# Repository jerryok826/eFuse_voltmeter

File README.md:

# eFuse Voltmeter

# eFuse Voltmeter in fault

## Project Description
eFuse_Voltmeter is a protection circuit for down stream electronic devices. A eFuse. The initial reason for the device was to protect a Ham radio when adjustmenting power mosfet transistors biasing. The fets can hit thermal run-way and destroy traces.

It can be powered from any DC power source between 5 to 25 volts. Its been test up to 6 amps.  At 5 amps the two inline mostfets drop 150millvolts each and the sense resistor drops 81 millvolts. Except for the mosfets it should work at much higher currents. So two the mosfets should upgraded. 

Features:
1. Reverse power protection.
2. Adjustable input over voltage input protection
3. Adjustable over current protection.
4. Voltage and current monitoring.
5. Output power control.
6. Output power disconnected on fault.
7. Audio alarm on fault.

When an over voltage or an over current event happens the board will disable its output. The fault state is latched until the control buttons is pressed. Apond a fault an audio alarm is also actived and a fault LEDs is lite. The fault value is indicted by its red measurement value and the fault RED led is lite. A fault is cleared by pressing the adjusement button. The output button needs to be press again to reable the boards output.
 
### Project Status
The project is basically complete. Working on improvements.

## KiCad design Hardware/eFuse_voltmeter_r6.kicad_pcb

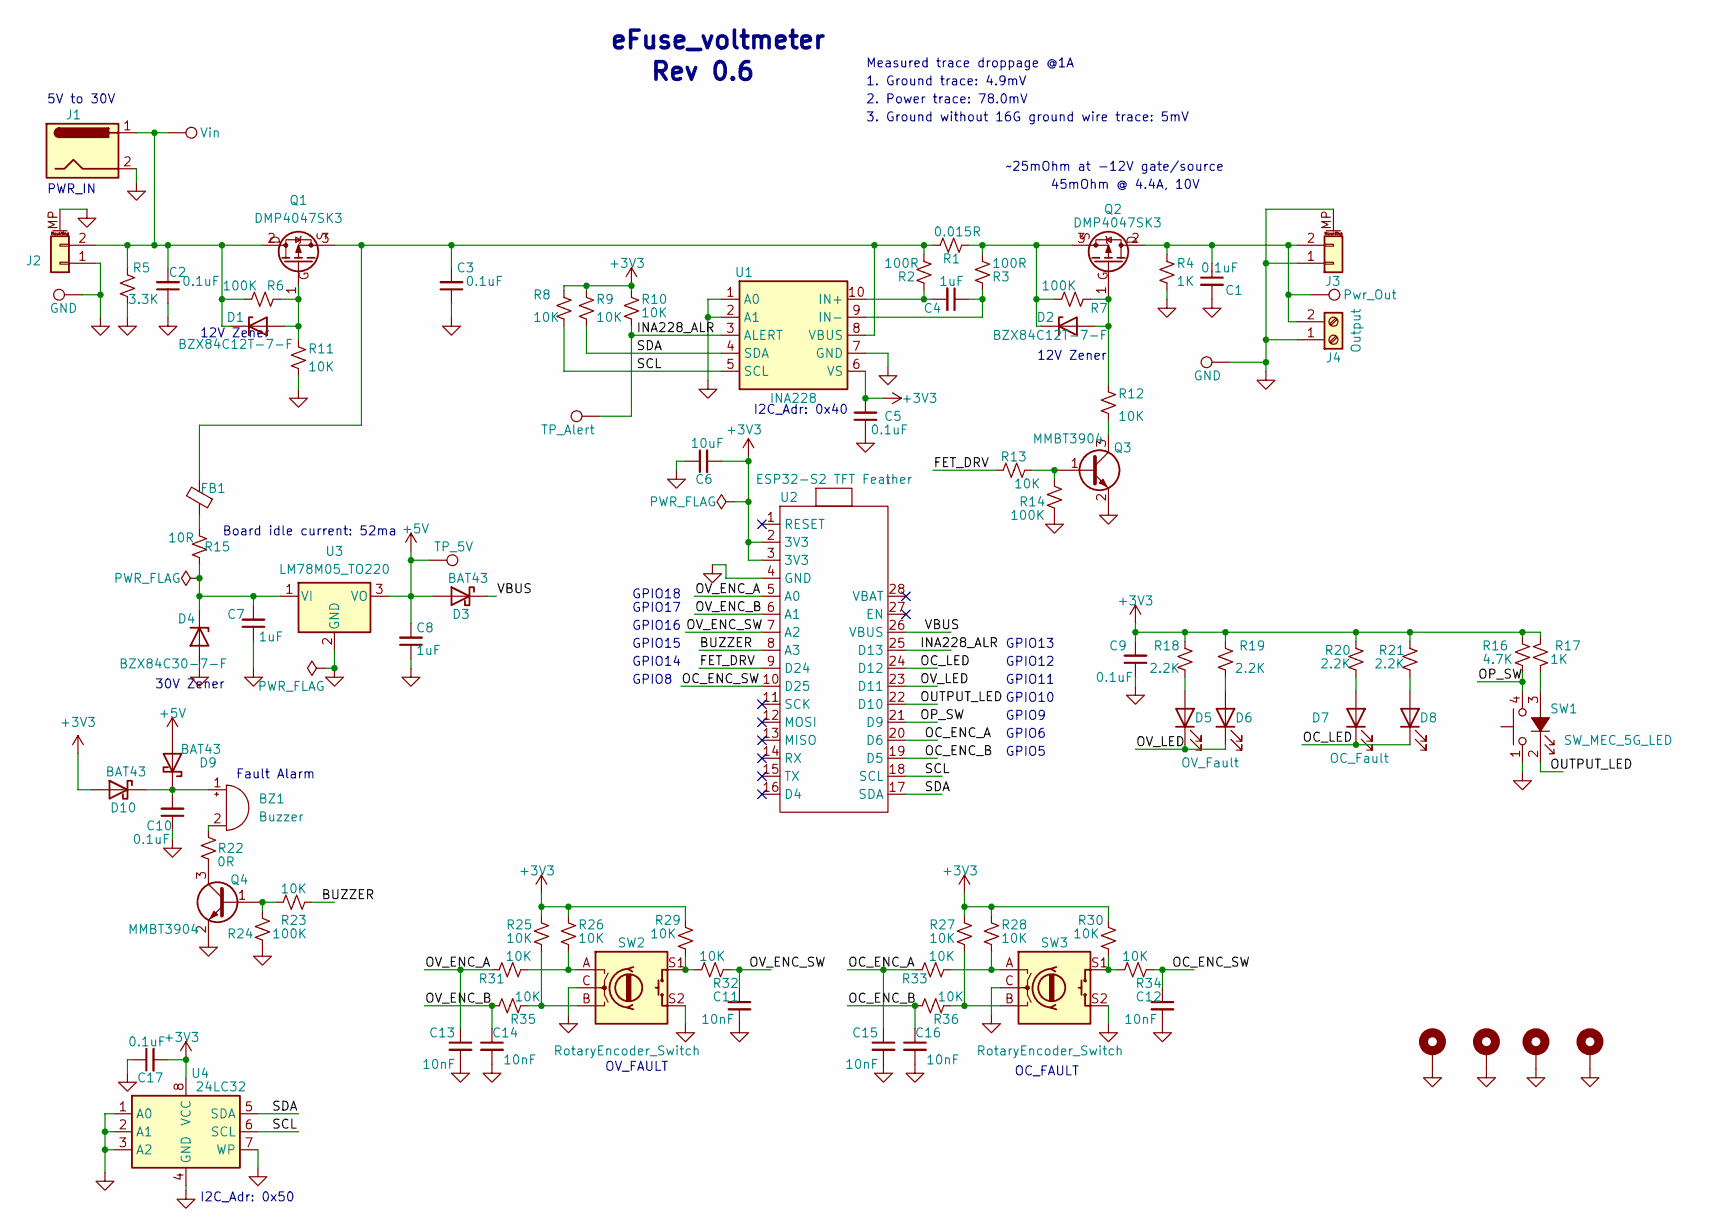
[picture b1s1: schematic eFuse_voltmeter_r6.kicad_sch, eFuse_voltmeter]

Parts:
BZ1: Buzzer; Buzzer_12x9.5RM7.6
C1, C2, C3, C5, C9, C10, C17: 0.1uF; C_0603_1608Metric_Pad1.08x0.95mm_HandSolder
C4, C7, C8: 1uF; C_0603_1608Metric_Pad1.08x0.95mm_HandSolder
C6: 10uF; C_0603_1608Metric_Pad1.08x0.95mm_HandSolder
C11, C12, C13, C14, C15, C16: 10nF; C_0603_1608Metric_Pad1.08x0.95mm_HandSolder
D1, D2: BZX84C12T-7-F; SOT-23
D3, D9, D10: BAT43; D_SOD-123
D4: BZX84C30-7-F; SOT-23
D5, D6: OV_Fault; LED_1206_3216Metric_Pad1.42x1.75mm_HandSolder
D7, D8: OC_Fault; LED_1206_3216Metric_Pad1.42x1.75mm_HandSolder
FB1: FerriteBead, 6A 1 9mΩ 33Ω@100MHz ±25% 1206 Ferrit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; L_1206_3216Metric_Pad1.42x1.75mm_HandSolder
GND1, GND2: GND; TestPoint_THTPad_D2.0mm_Drill1.0mm
H1, H2, H3, H4: MountingHole_Pad; MountingHole_2.7mm_M2.5_ISO14580_Pad
J1: INPUT_PWR; BarrelJack_GCT_DCJ200-10-A_Horizontal
J2, J3: Conn_01x02_MountingPin; Amass_XT60PW-M
J4: Output; TerminalBlock_bornier-2_P5.08mm
PWR_OUT1: Pwr_Out; TestPoint_THTPad_D2.0mm_Drill1.0mm
Q1, Q2: DMP4047SK3; TO-252-2
Q3, Q4: MMBT3904; SOT-23
R1: 0.015R; R_2512_6332Metric_Pad1.40x3.35mm_HandSolder; LCSC C159433
R2, R3: 100R; R_0603_1608Metric_Pad0.98x0.95mm_HandSolder
R4, R17: 1K; R_0603_1608Metric_Pad0.98x0.95mm_HandSolder
R5: 3.3K; R_0603_1608Metric_Pad0.98x0.95mm_HandSolder
R6, R7, R14, R24: 100K; R_0603_1608Metric_Pad0.98x0.95mm_HandSolder
R8, R9, R10, R11, R12, R13, R23, R25, R26, R27, R28, R29, R30, R31, R32, R33, R34, R35, R36: 10K; R_0603_1608Metric_Pad0.98x0.95mm_HandSolder
R15: 10R; R_1206_3216Metric_Pad1.30x1.75mm_HandSolder
R16: 4.7K; R_0603_1608Metric_Pad0.98x0.95mm_HandSolder
R18, R19, R20, R21: 2.2K; R_0603_1608Metric_Pad0.98x0.95mm_HandSolder
R22: 0R; R_0603_1608Metric_Pad0.98x0.95mm_HandSolder
SW1: SW_MEC_5G_LED; SW_PUSH_LED_6mm
SW2, SW3: RotaryEncoder_Switch; RotaryEncoder_Bourns_Vertical_PEC12R-3x17F-Sxxxx
TP_5V1: TP_5V; TestPoint_THTPad_D2.0mm_Drill1.0mm
TP_Alert1: TP_Alert; TestPoint_THTPad_D2.0mm_Drill1.0mm
U1: INA228; VSSOP-10_3x3mm_P0.5mm
U2: ESP32-S2 TFT Feather; Feather_RP2040
U3: LM78M05_TO220; TO-220-3_Horizontal_TabDown
U4: 24LC32; SOIC-8_3.9x4.9mm_P1.27mm
Vin1: Vin; TestPoint_THTPad_D2.0mm_Drill1.0mm

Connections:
+3V3: C5.2, C6.2, C9.2, C17.2, D10.2 (A), R8.1, R9.1, R10.1, R16.2, R17.2, R18.2, R19.2, R20.2, R21.2, R25.1, R26.1, R27.1, R28.1, R29.1, R30.1, U1.6 (VS), U2.2 (3V3), U2.3 (3V3), U4.8 (VCC)
+5V: C8.2, D3.2 (A), D9.2 (A), TP_5V1.1, U3.3 (VO)
/BUZZER: R23.2, U2.8 (A3)
/FET_DRV: R13.1, U2.9 (D24)
/INA228_ALR: R10.2, TP_Alert1.1, U1.3 (ALERT), U2.25 (D13)
/OC_ENC_A: C15.1, R33.1, U2.20 (D6)
/OC_ENC_B: C16.1, R36.1, U2.19 (D5)
/OC_ENC_SW: C12.1, R34.2, U2.10 (D25)
/OC_LED: D7.1 (K), D8.1 (K), U2.24 (D12)
/OP_SW: R16.1, SW1.4 (A), U2.21 (D9)
/OUTPUT_LED: SW1.2, U2.22 (D10)
/OV_ENC_A: C13.1, R31.1, U2.5 (A0)
/OV_ENC_B: C14.1, R35.1, U2.6 (A1)
/OV_ENC_SW: C11.1, R32.2, U2.7 (A2)
/OV_LED: D5.1 (K), D6.1 (K), U2.23 (D11)
/SCL: R8.2, U1.5 (SCL), U2.18 (SCL), U4.6 (SCL)
/SDA: R9.2, U1.4 (SDA), U2.17 (SDA), U4.5 (SDA)
/VBUS: D3.1 (K), U2.26 (VBUS)
GND: C1.2, C2.1, C3.1, C5.1, C6.1, C7.1, C8.1, C9.1, C10.1, C11.2, C12.2, C13.2, C14.2, C15.2, C16.2, C17.1, D4.1 (A), GND1.1, GND2.1, H1.1, H2.1, H3.1, H4.1, J1.2, J2.1, J2.MP (MountPin), J3.1, J3.MP (MountPin), J4.1, Q3.2 (E), Q4.2 (E), R4.2, R5.2, R11.2, R14.2, R24.2, SW1.1, SW2.C, SW2.S2, SW3.C, SW3.S2, U1.1 (A0), U1.2 (A1), U1.7 (GND), U2.4 (GND), U3.2 (GND), U4.1 (A0), U4.2 (A1), U4.3 (A2), U4.4 (GND), U4.7 (WP)
unnamed: BZ1.2 (+), R22.2
unnamed: BZ1.1 (-), C10.2, D9.1 (K), D10.1 (K)
unnamed: D1.1 (A), Q1.1 (G), R6.2, R11.1
unnamed: C2.2, D1.3 (K), J1.1, J2.2, Q1.2 (D), R5.1, R6.1, Vin1.1
unnamed: D2.1 (A), Q2.1 (G), R7.2, R12.1
unnamed: D2.3 (K), Q2.3 (S), R1.1, R3.1, R7.1
unnamed: C7.2, D4.3 (K), R15.1, U3.1 (VI)
unnamed: D5.2 (A), R18.1
unnamed: D6.2 (A), R19.1
unnamed: D7.2 (A), R20.1
unnamed: D8.2 (A), R21.1
unnamed: FB1.1, R15.2
unnamed: C1.1, J3.2, J4.2, PWR_OUT1.1, Q2.2 (D), R4.1
unnamed: C3.2, FB1.2, Q1.3 (S), R1.2, R2.1, U1.8 (VBUS)
unnamed: Q3.1 (B), R13.2, R14.1
unnamed: Q3.3 (C), R12.2
unnamed: Q4.1 (B), R23.1, R24.1
unnamed: Q4.3 (C), R22.1
unnamed: R25.2, R35.2, SW2.B
unnamed: R26.2, R31.2, SW2.A
unnamed: R27.2, R36.2, SW3.B
unnamed: R28.2, R33.2, SW3.A
unnamed: R29.2, R32.1, SW2.S1
unnamed: R30.2, R34.1, SW3.S1
unnamed: R17.1, SW1.3 (K)
unnamed: C4.2, R2.2, U1.10 (IN+)
unnamed: C4.1, R3.2, U1.9 (IN-)

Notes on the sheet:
Board idle current: 52ma
1. Ground trace: 4.9mV
I2C_Adr: 0x40
GPIO16
GPIO9
2. Power trace: 78.0mV
GPIO14
GPIO13
GPIO10
GPIO15
GPIO6
~25mOhm at -12V gate/source
PWR_IN
eFuse_voltmeter
GPIO11
Rev 0.6
GPIO17
Measured trace droppage @1A
5V to 30V
GPIO8
45mOhm @ 4.4A, 10V
12V Zener
OV_FAULT
GPIO12
Fault Alarm
I2C_Adr: 0x50
GPIO5
3. Ground without 16G ground wire trace: 5mV
GPIO18
30V Zener
OC_FAULT

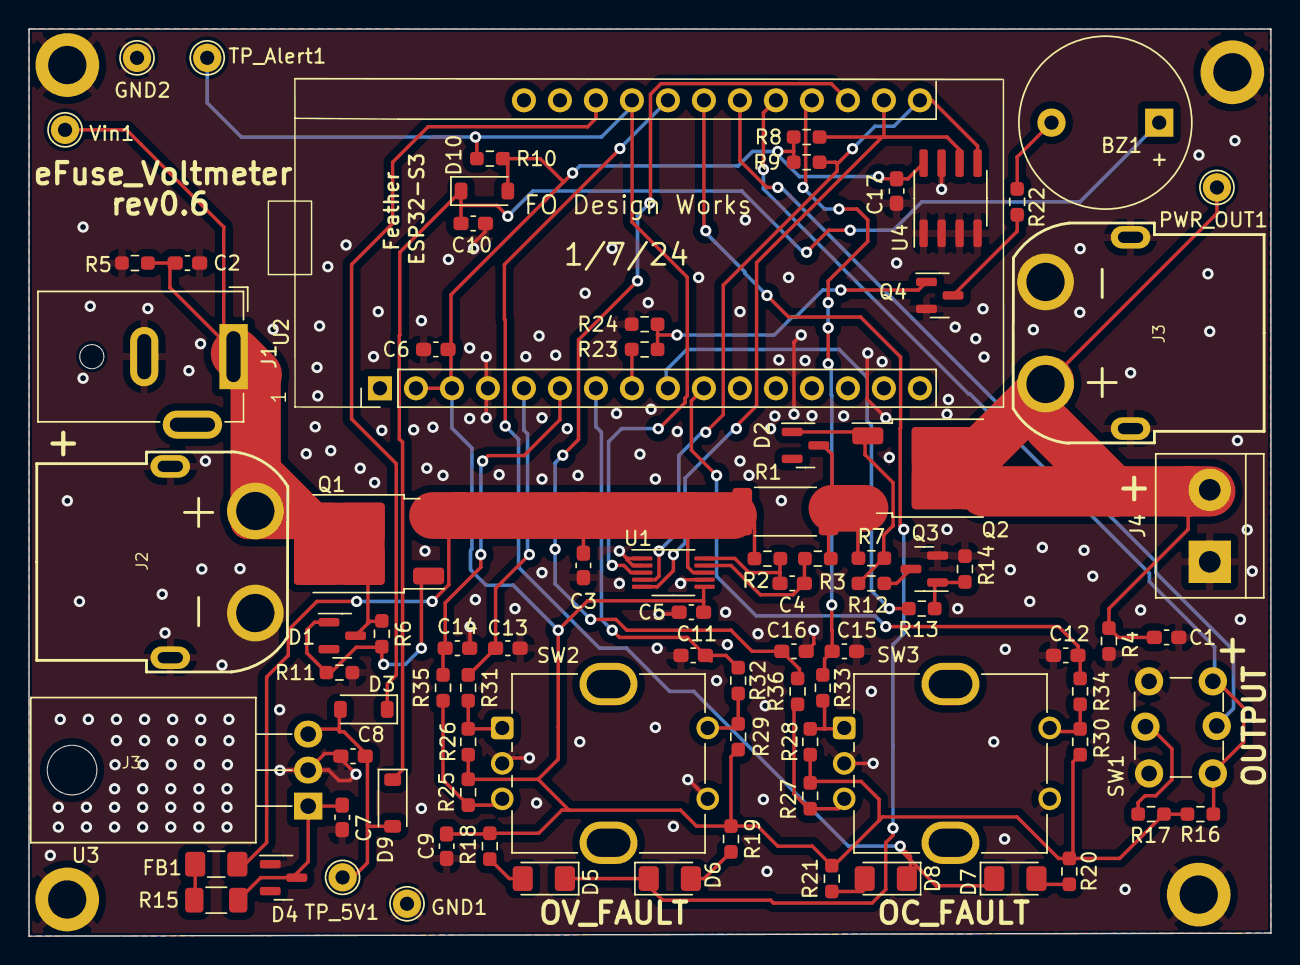
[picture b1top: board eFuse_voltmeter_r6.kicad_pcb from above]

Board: 2 copper layers, 87.6 x 64.0 mm, 90 parts (0 on the bottom side), 46 nets.

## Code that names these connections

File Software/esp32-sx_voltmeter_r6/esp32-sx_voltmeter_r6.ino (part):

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const float fet_on_resistance = 0.025;

// GPIO outputs
const int OC_led = 12;          // 7;       // GPIO7
const int OV_led = 11;          //8;        // GPIO
const int OUTPUT_led = 10;      // 10;      // GPIO
const int BUZZER = 15;          // 6;       // GPIO
const int FETDRV = 14;          // GPIO
const int INA228_ALR = 13;      // GPIO13  INA228_ALR

// GPIO inputs
const int OP_SW = 9;            // 18;       // GPIO18 ??
const int OV_ENC_SW = 16;       //12; // 25; // GPIO25 ??
const int OC_ENC_SW = 8;        //12; // 25; // GPIO25 ??

const int OV_ENC_A = 18; 
const int OV_ENC_B = 17;  
const int OC_ENC_A = 6; 
const int OC_ENC_B = 5; 

int ina228_alr_int_flag=0; // int flag

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void
output_led_set (int state)
{
  pinMode (OUTPUT_led, OUTPUT);
  if (state == 0) {
    digitalWrite (OUTPUT_led, HIGH);  // LED off
  }
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void
ov_led_set (int state)
{
  pinMode (OV_led, OUTPUT);
  if (state == 0) {
    digitalWrite (OV_led, HIGH);  // LED off
    ov_fault = 0;
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void
oc_led_set (int state)
{
  pinMode (OC_led, OUTPUT);
  if (state == 0) {
    digitalWrite (OC_led, HIGH); // LED off
    oc_fault = 0;
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void
buzzer_set (int state)
{
  pinMode (BUZZER, OUTPUT);
  if (state == 0) {
    digitalWrite (BUZZER, LOW); // off
  }
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  Serial.printf("eFuse_voltmeter Init, Built: %s %s\n",__DATE__,__TIME__);

  // Dont know way this is required, Without it OV enc does not work. GPIO18
  //pinMode (OV_ENC_A, INPUT);  

  button.begin (OP_SW);
  button.setToggleState (0);    // set initial state 0 or 1
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  pinMode (TFT_I2C_POWER, OUTPUT);
  digitalWrite (TFT_I2C_POWER, HIGH);

  pinMode (OP_SW, INPUT_PULLUP);
  pinMode (OV_ENC_SW, INPUT_PULLUP); // AL_RST_SW, INPUT);
  pinMode (OC_ENC_SW, INPUT_PULLUP); // AL_RST_SW, INPUT);

  // Set encoder inputs
#if 0
//  pinMode (OV_ENC_B, INPUT_PULLUP); // Does not cause ENC problems if commented out
  pinMode (OV_ENC_A, INPUT); //18, INPUT); // Voltage ENC, Not sure if or why we need this

//  pinMode (OC_ENC_B, INPUT_PULLUP); // Does not cause ENC problems if commented out
//  pinMode (OC_ENC_A, INPUT_PULLUP); // Does not cause ENC problems if commented out
#endif
  
//  i2c_scan (); // debug routines
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
  // enable fault interrupt
  ina228_alr_int_flag=0;
  pinMode(INA228_ALR, INPUT_PULLUP);
  attachInterrupt(INA228_ALR, isr, FALLING);
}

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
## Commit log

2023-12-11 Create Pictures
2024-02-16 major update
2024-02-21 code clean up
2024-02-22 clean up
2024-02-22 remove some files
2024-02-22 swap in a file
2024-02-22 add captions to photos
